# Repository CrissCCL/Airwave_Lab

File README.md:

# 🔭 Bluetooth / BLE & RF Research Toolkit

> ⚠️ **Important:** This repository is strictly for **educational, analysis, and defensive research**.  
> It **does NOT** contain instructions or tools to jam, block, or interfere with radio communications.  
> Active interference (jamming, blocking) is illegal in many jurisdictions. Always obtain written authorization for any active tests and restrict them to isolated, shielded testbeds.

## 📖 Overview
This project — developed using **nRF24L01** modules and **ESP32** boards — gathers documentation and safe experiments for learning about Bluetooth/BLE and RF signaling in a legal, ethical way. The emphasis is on passive monitoring, not packet analysis, rather on protocol learning, and building controlled lab exercises for students and researchers.

Goals:
- Understand BLE and RF packet structures and behaviors.
- Perform **passive** captures and logging using ESP32 and nRF24L01 hardware in permitted environments.
- Create reproducible lab exercises to teach secure pairing, privacy addresses, and interference mitigation.
- Provide safe, legal guidance for setting up an isolated test environment.

> ⚠️ This repository will never provide instructions to build or operate jammers or active interference devices.

## 📂 Contents
- `/Hardware` →  schematic, Gerbers for ESP32 + nRF24L01.
- `/code_jmmV1_2` → C code for ESP32 (Arduino environment). Fixed code V1.2.

## 🔗 Companion Scanner Project

For passive monitoring and visualization of BLE activity and relative RF energy
in the 2.4 GHz ISM band, see the companion scanner repository:

**[ESP32 BLE and 2.4 GHz RF Activity Scanner](https://github.com/CrissCCL/ESP32_BLE_RF24_Activity_Scanner)**

The scanner provides real-time BLE monitoring, relative RF-energy detection with
nRF24L01 modules, a Processing 4 interface, CSV recording, and MATLAB/Python
tools for offline analysis. It can be used alongside the controlled experiments
documented in Airwave Lab to observe and compare RF activity.

## 📊 Project Status
| Component                  | Status                      |
|---------------------------|-----------------------------|
| ESP32 passive scanner examples   | ✅ Completed               |
| nRF24L01 observation examples    | ✅ Completed             |
| Device assembly and electronic testing   | ✅ Completed               |
| Legal & ethics write-up   | ✅ Completed                |
| Spectrum captures         | ✅ Completed               |
| Measurement photos        | ✅ Completed            |
| Fix code    | ✅ Completed            |
| Active interference research     | 🚫 Not included (forbidden)|

## ⚙️ System Description
- **Controller:** ESP32  
- **Transceiver Module:** nRF24L01+ (PA/LNA version)  
- **Function:** Generates controlled interference patterns for BLE and Bluetooth channels  
- **Operating Bands:** 2.400–2.4835 GHz (ISM band)  
- **BLE Channels:** {2, 26, 80}  
- **Bluetooth Channels:** {32, 34, 46, 48, 50, 52, 0, 1, 2, 4, 6, 8, 22, 24, 26, 28, 30, 74, 76, 78, 80}  
- **Measurement:** Tested with Anritsu MS2760A-0070 Spectrum Analyzer at Airwave Lab  

## 🧰 Hardware & Tools (recommended for passive analysis)
- **ESP32** development boards — used for BLE scanning and passive logging.
- **nRF24L01** modules — for hobby RF monitoring in permitted contexts (note: nRF24 uses its own non-Bluetooth RF stack).
- Shielded enclosure / Faraday box for any active experiments.

## 🔬 Measurement methodology (high-level)
- Measurements were taken using a calibrated **spectrum analyzer** and suitable antennas.  
- Experiments were performed in a controlled environment (shielded enclosure / isolated lab) and with the appropriate authorizations.  
- Captures include frequency averaged power spectral density (PSD).  
- **No** step-by-step operational instructions or parameter sets for unauthorized RF interference are included.

### 📸 Setup photos laboratory

<table>
  <tr>
    <td align="center">
      <br>
      <sub>Anritsu MS2760A-0070</sub>
    </td>
    <td align="center">
      <br>
      <sub>Anechoic chamber</sub>
    </td>
  </tr>
</table>

### 🔌 Power-off / Setup Overview

<p align="center">
  <br>
  <sub>Power-off device noise floor spectrum measurement</sub>
</p>

### 📈 Measurement Overview — BLE & Bluetooth

The spectrum analyzer tests documented below capture the emissions produced by the device in the **2.4 GHz ISM band (2.400 – 2.4835 GHz)**.  
During each test mode, the device performed a **frequency sweep across BLE and Bluetooth channels** to evaluate spectral behavior and signal distortions.

- **BLE (Bluetooth Low Energy)**: 40 channels, **2 MHz spacing**, from **2402 MHz to 2480 MHz**.  
- **Bluetooth Classic (BR/EDR)**: 79 channels, **1 MHz spacing**, from **2402 MHz to 2480 MHz**.

> ⚠️ Note: The device operation is shown for academic and educational purposes only. No instructions or parameters are provided to operate or reproduce emissions. All tests were conducted in a controlled laboratory environment with proper authorization.

### 📸 Measurement Photos — BLE

<table>
  <tr>
    <td align="center">
      <br>
      <sub>BLE — Capture 1</sub>
    </td>
    <td align="center">
      <br>
      <sub>BLE — Capture 2</sub>
    </td>
  </tr>
  <tr>
    <td align="center">
      <br>
      <sub>BLE — Capture 3</sub>
    </td>
    <td></td>
  </tr>
</table>

### 📸 Measurement Photos — Bluetooth

<table>
  <tr>
    <td align="center">
      <br>
      <sub>Bluetooth — Capture 1</sub>
    </td>
    <td align="center">
      <br>
      <sub>Bluetooth — Capture 2</sub>
    </td>
  </tr>
  <tr>
    <td align="center">
      <br>
      <sub>Bluetooth — Capture 3</sub>
    </td>
    <td></td>
  </tr>
</table>

### 📈 Measurement Results (Summary)

- **Instrument:** Anritsu MS2760A-0070 spectrum analyzer.  
- **Captured data:** spectrum analyzer traces highlighting distortion in BLE/Bluetooth bands during device operation.  
- **Observed effects:** spectral broadening, spurious components and harmonics consistent with strong in-band emissions. These effects were recorded for documentation and analysis purposes only.  
- **Test modes:** the device was evaluated under several modes; during each mode the device performed sweeps across channels to observe frequency-dependent behavior. *(Operational parameters and control signals are intentionally omitted from this repository.)*  
- **Purpose:** these measurements inform detection/mitigation strategies and support responsible research into electromagnetic compatibility and spectrum monitoring.

> ⚠️ Note: Raw operation logs or parameter sets that would enable reproduction of emissions are excluded from this repository.

### 🙏 Acknowledgments

Special thanks to the **[Laboratorio de Comunicaciones Inalámbricas — EIE PUCV](https://eie.pucv.cl/investigacion/lineas-de-investigacion-y-laboratorios/laboratorio-de-comunicaciones-inalambricas/)**  
for providing access to facilities, the **Anechoic Chamber**, and the **Anritsu MS2760A-0070 Spectrum Analyzer** used in these experiments.

## 🖼️ 3D PCB Render (version 3)

<table>
  <tr>
    <td align="center">
      <br>
      <sub>PCB render — front (v3)</sub>
    </td>
    <td align="center">
      <br>
      <sub>PCB render — back (v3)</sub>
    </td>
  </tr>
</table>

## ⚡ Physical Prototype

<table>
  <tr>
    <td align="center">
      <br>
      <sub>Device — front</sub>
    </td>
    <td align="center">
      <br>
      <sub>Device — back</sub>
    </td>
  </tr>
</table>

## ⚖️ Legal & Ethical Guidelines
- Do not capture or analyze traffic from third-party devices without explicit permission.  
- Passive monitoring may still be subject to local laws — check your national telecom regulations.  
- Keep careful logs of tests, dates, and authorizations.  
- Perform any active tests only inside a shielded enclosure and with written consent.

# ⚖️ Legal & Regulatory References

This project is intended strictly for **educational purposes**.  
Operating or building radio interference devices without authorization is **illegal** in most jurisdictions.  
Below are links to relevant regulatory frameworks:

---

## 🇨🇱 Chile
- [Ley N° 18.168 — Ley General de Telecomunicaciones (BCN)](https://www.bcn.cl/leychile/navegar?idNorma=29582)  
- [Subsecretaría de Telecomunicaciones (SUBTEL) — Normas y Leyes](https://www.subtel.gob.cl/normas-y-leyes/)

---

## 🇺🇸 United States
- [47 CFR Part 15 — Radio Frequency Devices (eCFR)](https://www.ecfr.gov/current/title-47/chapter-I/subchapter-A/part-15)  
- [FCC — Rules & Regulations Overview](https://www.fcc.gov/rules-regulations)

---

## 🇪🇺 European Union
- [Directive (EU) 2018/1972 — European Electronic Communications Code (EECC)](https://eur-lex.europa.eu/legal-content/EN/TXT/?uri=CELEX%3A32018L1972)  
- [Directive 2014/53/EU — Radio Equipment Directive (RED)](https://eur-lex.europa.eu/legal-content/EN/TXT/?uri=CELEX%3A32014L0053)

---

## 🔒 Disclaimer
These references are provided for **informational purposes only**.  
- Always verify the current applicable law in your jurisdiction.  
- Obtain explicit **written authorization** before performing any active test involving RF emissions.  
- Limit all experiments to **controlled, shielded laboratory environments**.

## 🤝 Support projects
 Support me on Patreon [https://www.patreon.com/c/CrissCCL](https://www.patreon.com/c/CrissCCL)

## 📜 License
MIT License

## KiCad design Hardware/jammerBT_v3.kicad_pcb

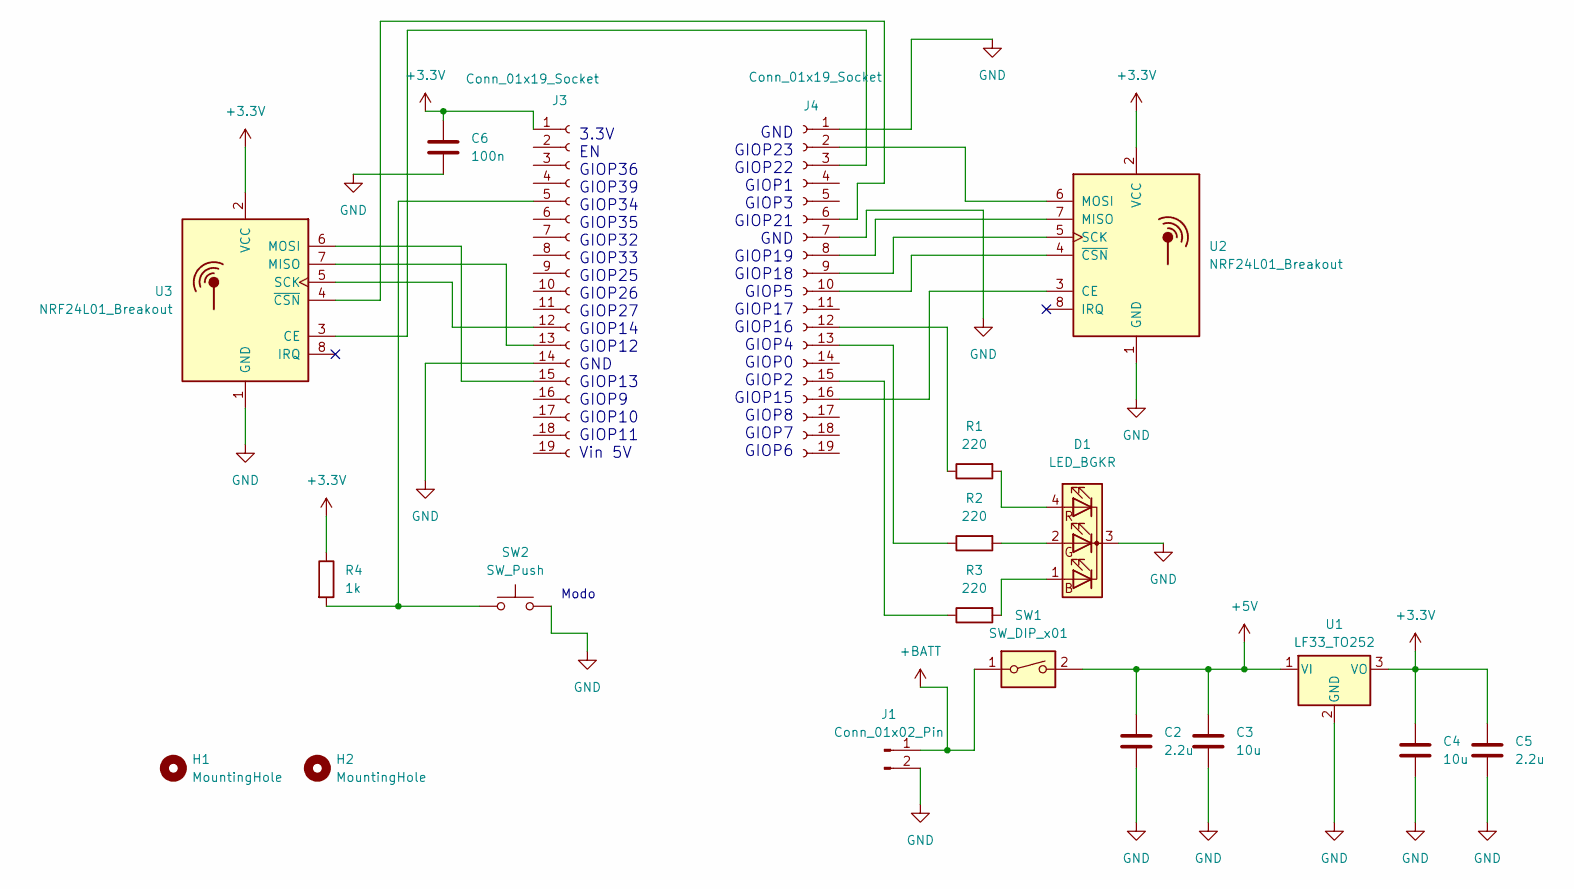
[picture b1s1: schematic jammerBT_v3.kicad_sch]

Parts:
C2, C5: 2.2u; C_Elec_4x5.4
C3, C4: 10u; C_Elec_4x5.4
C6: 100n; C_0805_2012Metric_Pad1.18x1.45mm_HandSolder
D1: LED_BGKR; LED_D5.0mm-4_RGB_Wide_Pins
H1, H2: MountingHole; MountingHole_3.2mm_M3_DIN965_Pad
J1: Conn_01x02_Pin; conector_pad
J3, J4: Conn_01x19_Socket; PinHeader_1x19_P2.54mm_Vertical
R1, R2, R3: 220; R_1206_3216Metric_Pad1.30x1.75mm_HandSolder
R4: 1k; R_1206_3216Metric_Pad1.30x1.75mm_HandSolder
SW1: SW_DIP_x01; spst 1
SW2: SW_Push; SW_Push_1P1T_NO_CK_KSC7xxJ
U1: LF33_TO252; TO-252-2
U2, U3: NRF24L01_Breakout; nRF24L01_Breakout

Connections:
+3.3V: C4.1, C5.1, C6.1, J3.1, R4.1, U1.3 (VO), U2.2 (VCC), U3.2 (VCC)
+5V: C2.1, C3.1, SW1.2, U1.1 (VI)
+BATT: J1.1, SW1.1
GND: C2.2, C3.2, C4.2, C5.2, C6.2, D1.3 (K), J1.2, J3.14, J4.1, J4.7, SW2.2, U1.2 (GND), U2.1 (GND), U3.1 (GND)
unnamed: D1.1 (BA), R3.2
unnamed: D1.2 (GA), R2.2
unnamed: D1.4 (RA), R1.2
unnamed: J3.5, R4.2, SW2.1
unnamed: J3.12, U3.5 (SCK)
unnamed: J3.13, U3.7 (MISO)
unnamed: J3.15, U3.6 (MOSI)
unnamed: J4.2, U2.6 (MOSI)
unnamed: J4.3, U3.3 (CE)
unnamed: J4.6, U3.4 (~CSN)
unnamed: J4.8, U2.7 (MISO)
unnamed: J4.9, U2.5 (SCK)
unnamed: J4.10, U2.4 (~CSN)
unnamed: J4.12, R1.1
unnamed: J4.13, R2.1
unnamed: J4.15, R3.1
unnamed: J4.16, U2.3 (CE)

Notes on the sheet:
Modo
3.3V EN GIOP36 GIOP39 GIOP34 GIOP35 GIOP32 GIOP33 GIOP25 GIOP26 GIOP27 GIOP14 GIOP12 GND GIOP13 GIOP9 GIOP10 GIOP11 Vin 5V
GND GIOP23 GIOP22 GIOP1 GIOP3 GIOP21 GND GIOP19 GIOP18 GIOP5 GIOP17 GIOP16 GIOP4 GIOP0 GIOP2 GIOP15 GIOP8 GIOP7 GIOP6

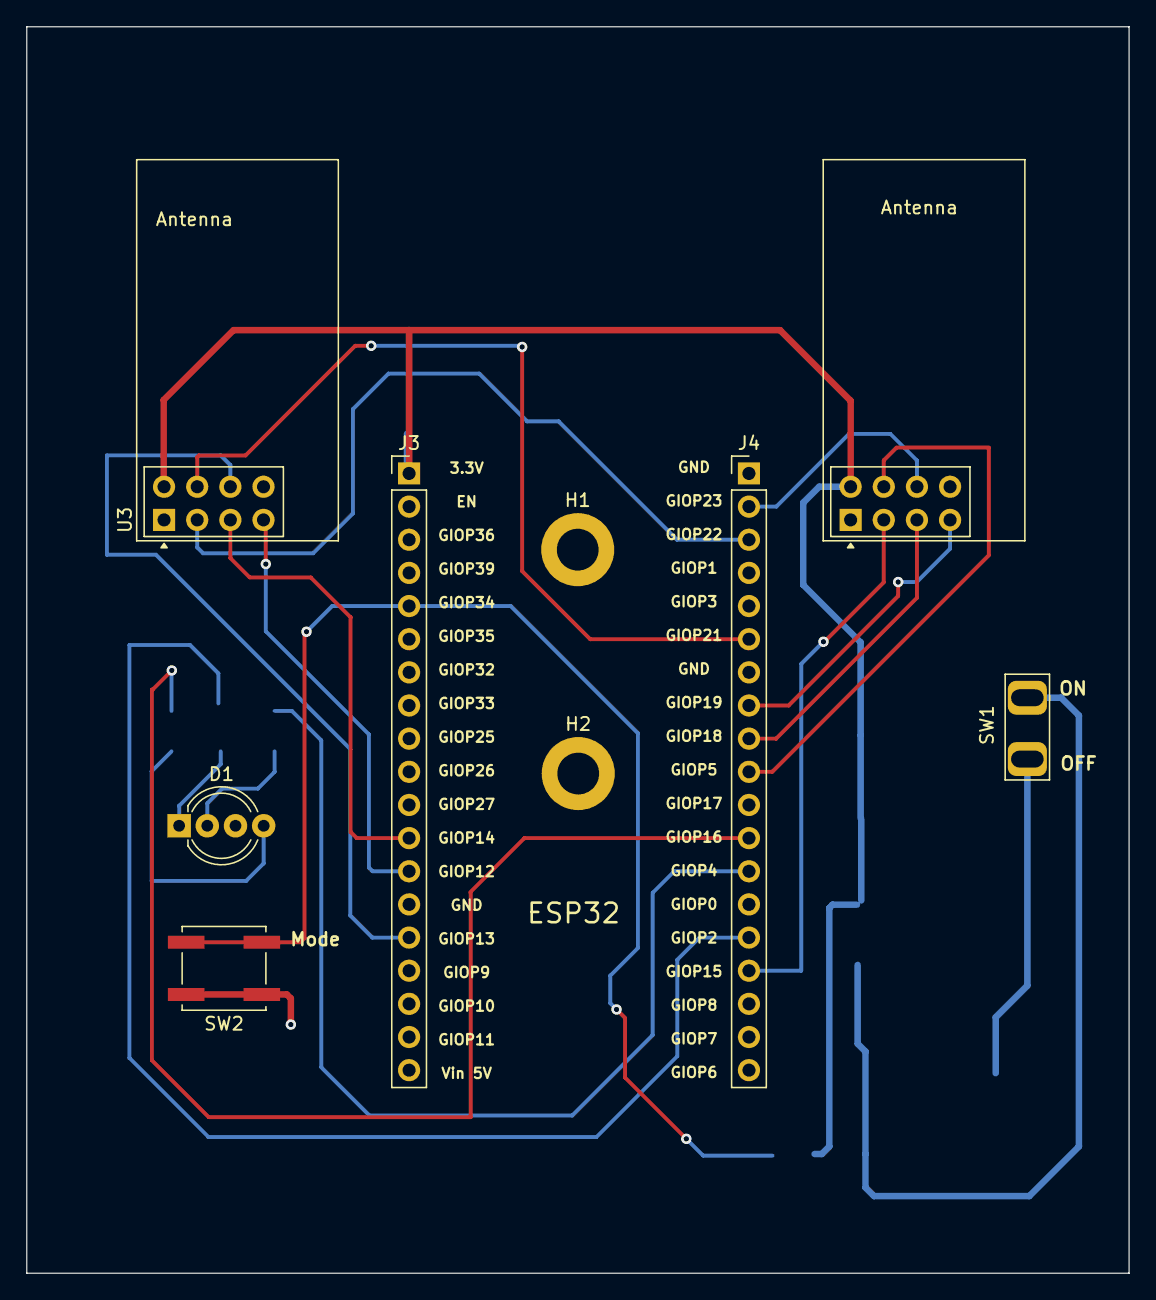
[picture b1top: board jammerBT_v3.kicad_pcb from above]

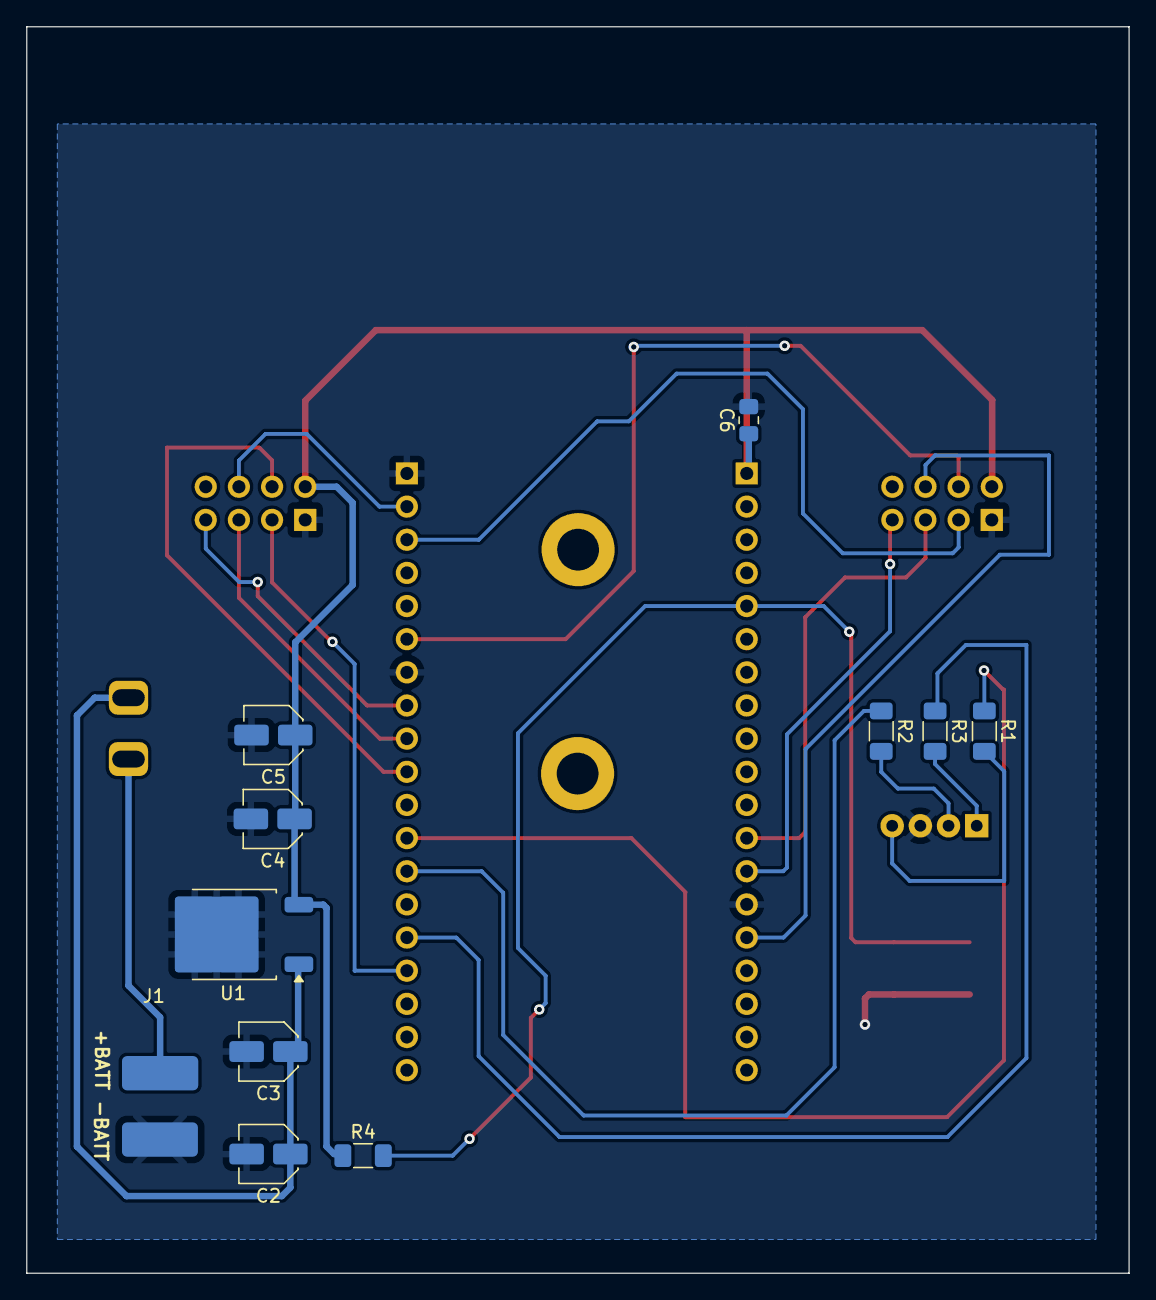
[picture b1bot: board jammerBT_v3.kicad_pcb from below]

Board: 2 copper layers, 84.5 x 95.5 mm, 20 parts (11 on the bottom side), 21 nets.

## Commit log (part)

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2025-09-30 Rename pectrum_analyzer.jpg to spectrum_analyzer.jpg
2025-09-30 Actualizar README.md
2025-10-24 Update image sources to use raw GitHub URLs
2026-01-05 Add support projects section to README
    Added a section for supporting projects via Patreon.
2026-02-07 Update LICENSE
